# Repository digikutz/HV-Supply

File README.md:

HV-Supply
=========

A simple DIY bench top High voltage supply for tubes etc.

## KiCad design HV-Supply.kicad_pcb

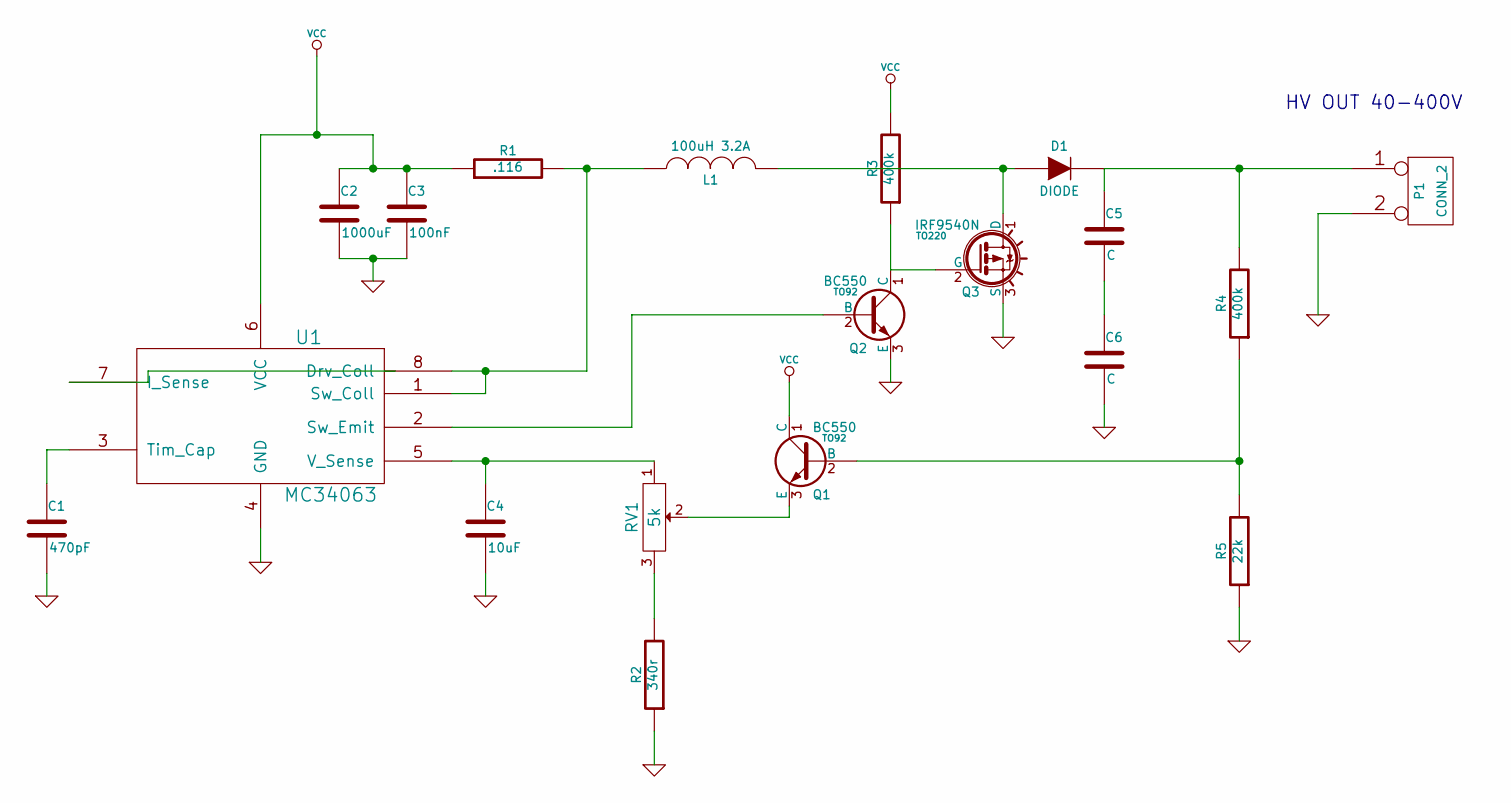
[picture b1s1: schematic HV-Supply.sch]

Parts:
C1: 470pF
C2: 1000uF
C3: 100nF
C4: 10uF
C5, C6: C
D1: DIODE
L1: 100uH 3.2A
P1: CONN_2
Q1, Q2: BC550; TO92
Q3: IRF9540N; TO220
R1: .116
R2: 340r
R3, R4: 400k
R5: 22k
RV1: 5k
U1: MC34063

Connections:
GND: C1.2, C2.2, C3.2, C4.2, C6.2, P1.2 (PM), Q2.3 (E), Q3.3 (S), R2.1, R5.1, U1.4 (GND)
unnamed: D1.1 (A), L1.2, Q3.1 (D)
unnamed: Q2.1 (C), Q3.2 (G), R3.1
unnamed: Q2.2 (B), U1.2 (Sw_Emit)
unnamed: Q1.2 (B), R4.1, R5.2
unnamed: R2.2, RV1.3
unnamed: C5.2, C6.1
unnamed: C5.1, D1.2 (K), P1.1, R4.2
unnamed: Q1.3 (E), RV1.2
unnamed: C4.1, RV1.1, U1.5 (V_Sense)
unnamed: C1.1, U1.3 (Tim_Cap)
unnamed: L1.1, R1.2, U1.1 (Sw_Coll), U1.8 (Drv_Coll)
VCC: C2.1, C3.1, Q1.1 (C), R1.1, R3.2, U1.6 (VCC)

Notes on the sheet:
HV OUT 40-400V

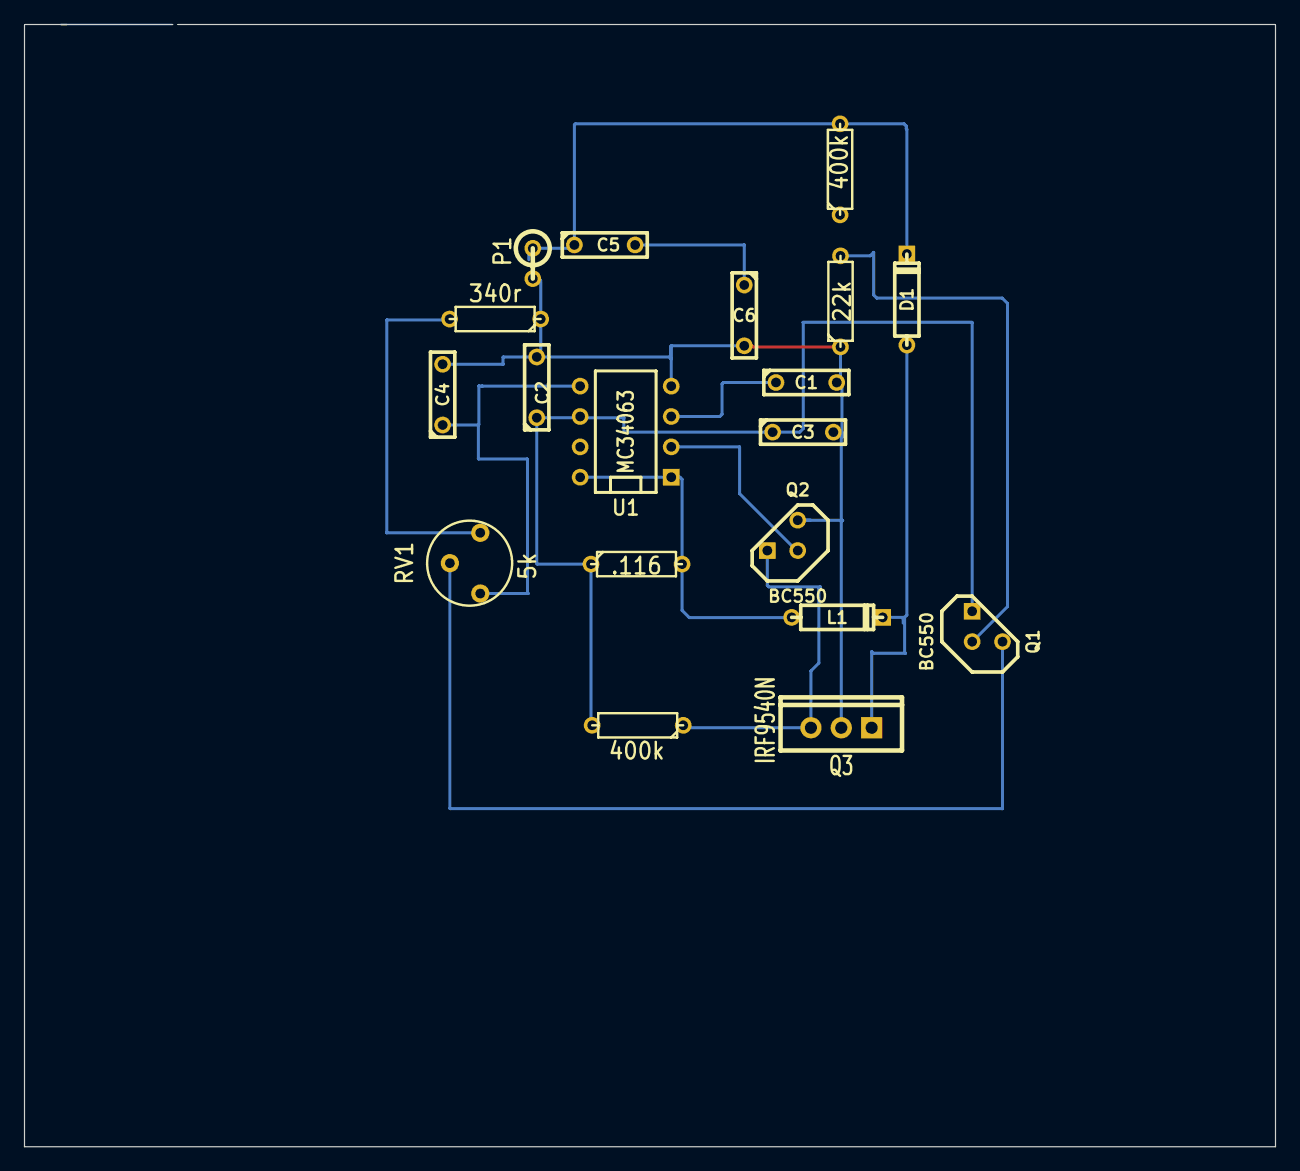
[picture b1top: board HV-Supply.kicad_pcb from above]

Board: 2 copper layers, 104.6 x 93.9 mm, 19 parts (0 on the bottom side), 13 nets.

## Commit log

2014-04-11 PCB's in progress
